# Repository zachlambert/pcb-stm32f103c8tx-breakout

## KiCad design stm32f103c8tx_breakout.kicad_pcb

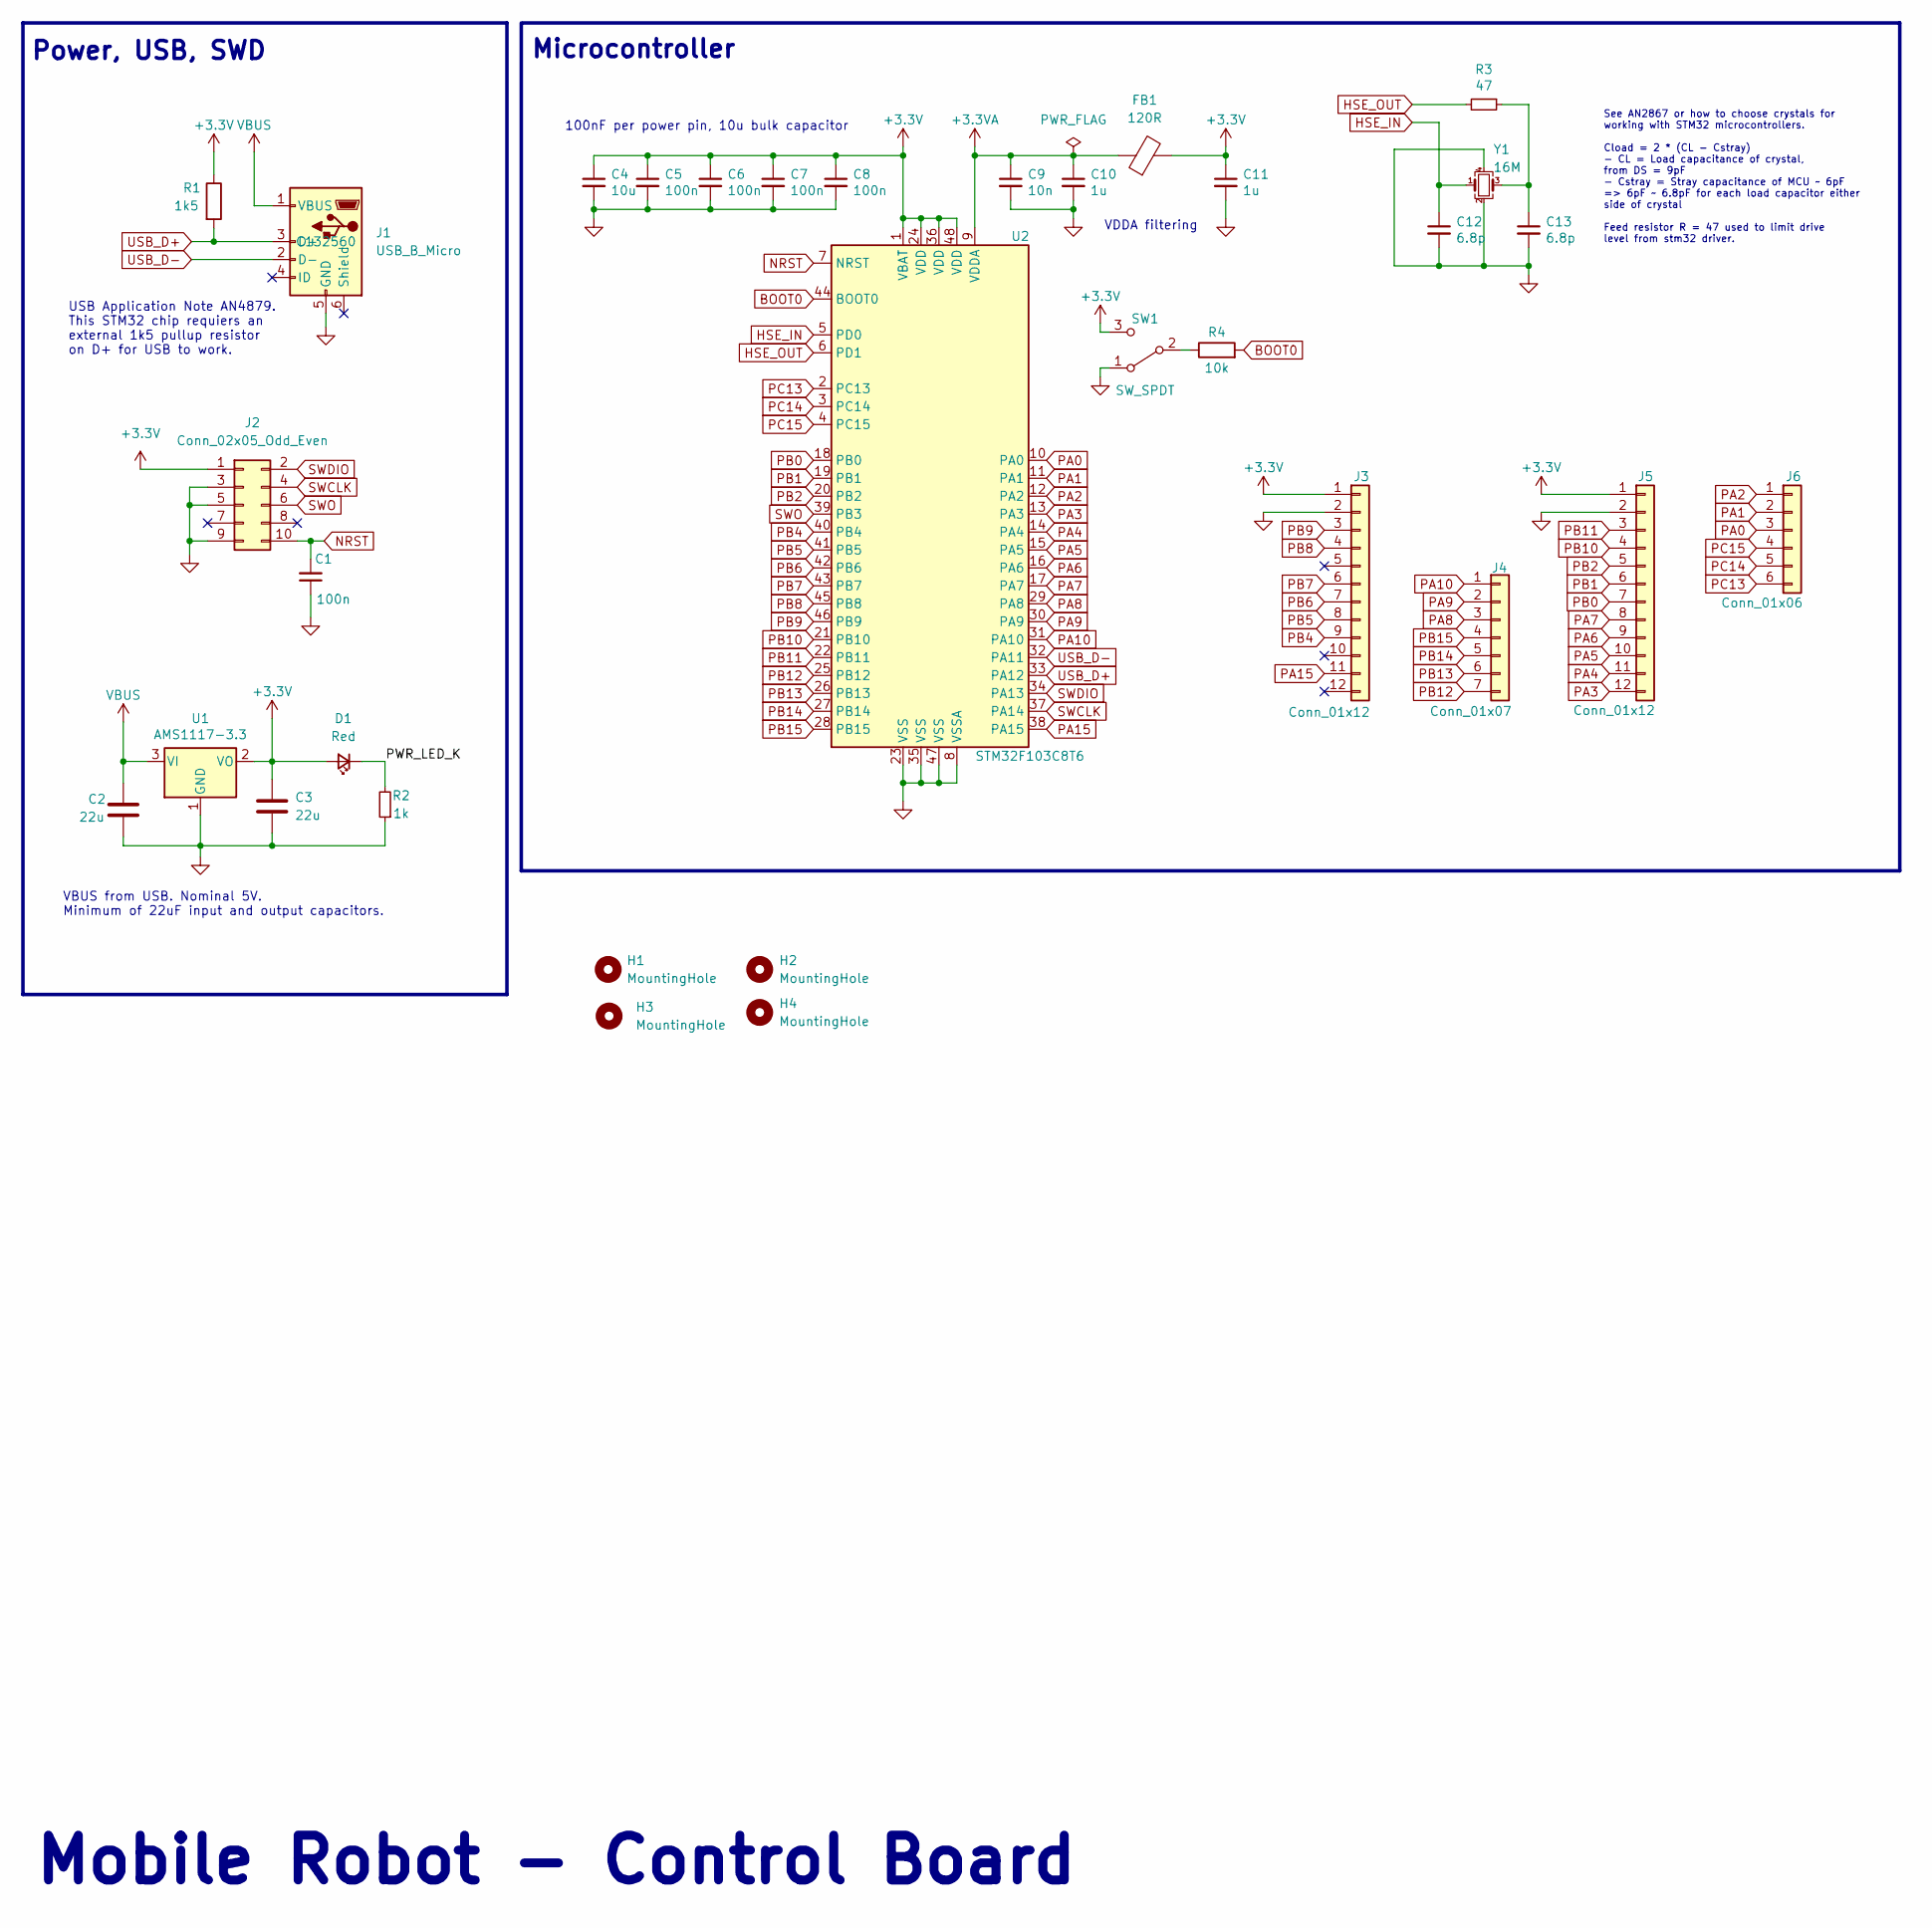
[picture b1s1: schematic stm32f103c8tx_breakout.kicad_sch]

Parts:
C1, C5, C6, C7, C8: 100n; C_0402_1005Metric
C2, C3: 22u; C_0805_2012Metric
C4: 10u; C_0603_1608Metric
C9: 10n; C_0402_1005Metric
C10, C11: 1u; C_0402_1005Metric
C12, C13: 6.8p; C_0402_1005Metric
D1: Red; D_0603_1608Metric
FB1: 120R; L_0603_1608Metric
H1, H2, H3, H4: MountingHole; MountingHole_3.2mm_M3
J1: USB_B_Micro; USB_Micro-B_Molex_47346-0001; LCSC C132560
J2: Conn_02x05_Odd_Even; PinHeader_2x05_P2.54mm_Vertical; LCSC C492422
J3, J5: Conn_01x12; PinSocket_1x12_P2.54mm_Vertical
J4: Conn_01x07; PinSocket_1x07_P2.54mm_Vertical
J6: Conn_01x06; PinSocket_1x06_P2.54mm_Vertical
R1: 1k5; R_0402_1005Metric
R2: 1k; R_0402_1005Metric
R3: 47; R_0402_1005Metric
R4: 10k; R_0402_1005Metric
SW1: SW_SPDT; SW_SPDT_PCM12
U1: AMS1117-3.3; SOT-223-3_TabPin2; LCSC C6186
U2: STM32F103C8T6; LQFP-48_7x7mm_P0.5mm; LCSC C8734
Y1: 16M; Crystal_SMD_3225-4Pin_3.2x2.5mm; LCSC C13738

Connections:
+3.3VA: C9.1, C10.1, FB1.1, U2.9 (VDDA)
+3V3: C3.1, C4.1, C5.1, C6.1, C7.1, C8.1, C11.1, D1.2 (A), FB1.2, J2.1, J3.1, J5.1, R1.1, SW1.3 (C), U1.2 (VO), U2.1 (VBAT), U2.24 (VDD), U2.36 (VDD), U2.48 (VDD)
/PWR_LED_K: D1.1 (K), R2.2
BOOT0: R4.2, U2.44 (BOOT0)
GND: C1.1, C2.2, C3.2, C4.2, C5.2, C6.2, C7.2, C8.2, C9.2, C10.2, C11.2, C12.2, C13.2, J1.5 (GND), J2.3, J2.5, J2.9, J3.2, J5.2, R2.1, SW1.1 (A), U1.1 (GND), U2.8 (VSSA), U2.23 (VSS), U2.35 (VSS), U2.47 (VSS), Y1.2, Y1.4
HSE_IN: C12.1, U2.5 (PD0), Y1.1
HSE_OUT: R3.2, U2.6 (PD1)
NRST: C1.2, J2.10, U2.7 (NRST)
unnamed: C13.1, R3.1, Y1.3
unnamed: R4.1, SW1.2 (B)
PA0: J6.3, U2.10 (PA0)
PA1: J6.2, U2.11 (PA1)
PA2: J6.1, U2.12 (PA2)
PA3: J5.12, U2.13 (PA3)
PA4: J5.11, U2.14 (PA4)
PA5: J5.10, U2.15 (PA5)
PA6: J5.9, U2.16 (PA6)
PA7: J5.8, U2.17 (PA7)
PA8: J4.3, U2.29 (PA8)
PA9: J4.2, U2.30 (PA9)
PA10: J4.1, U2.31 (PA10)
PA15: J3.11, U2.38 (PA15)
PB0: J5.7, U2.18 (PB0)
PB1: J5.6, U2.19 (PB1)
PB2: J5.5, U2.20 (PB2)
PB4: J3.9, U2.40 (PB4)
PB5: J3.8, U2.41 (PB5)
PB6: J3.7, U2.42 (PB6)
PB7: J3.6, U2.43 (PB7)
PB8: J3.4, U2.45 (PB8)
PB9: J3.3, U2.46 (PB9)
PB10: J5.4, U2.21 (PB10)
PB11: J5.3, U2.22 (PB11)
PB12: J4.7, U2.25 (PB12)
PB13: J4.6, U2.26 (PB13)
PB14: J4.5, U2.27 (PB14)
PB15: J4.4, U2.28 (PB15)
PC13: J6.6, U2.2 (PC13)
PC14: J6.5, U2.3 (PC14)
PC15: J6.4, U2.4 (PC15)
SWCLK: J2.4, U2.37 (PA14)
SWDIO: J2.2, U2.34 (PA13)
SWO: J2.6, U2.39 (PB3)
USB_D+: J1.3 (D+), R1.2, U2.33 (PA12)
USB_D-: J1.2 (D-), U2.32 (PA11)
VBUS: C2.1, J1.1 (VBUS), U1.3 (VI)

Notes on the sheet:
USB Application Note AN4879. This STM32 chip requiers an external 1k5 pullup resistor on D+ for USB to work.
VDDA filtering
Power, USB, SWD
See AN2867 or how to choose crystals for working with STM32 microcontrollers. Cload = 2 * (CL - Cstray) - CL = Load capacitance of crystal, from DS = 9pF - Cstray = Stray capacitance of MCU ~ 6pF => 6pF ~ 6.8pF for each load capacitor either side of crystal Feed resistor R = 47 used to limit drive 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
Mobile Robot - Control Board
100nF per power pin, 10u bulk capacitor
Microcontroller
VBUS from USB. Nominal 5V. Minimum of 22uF input and output capacitors.

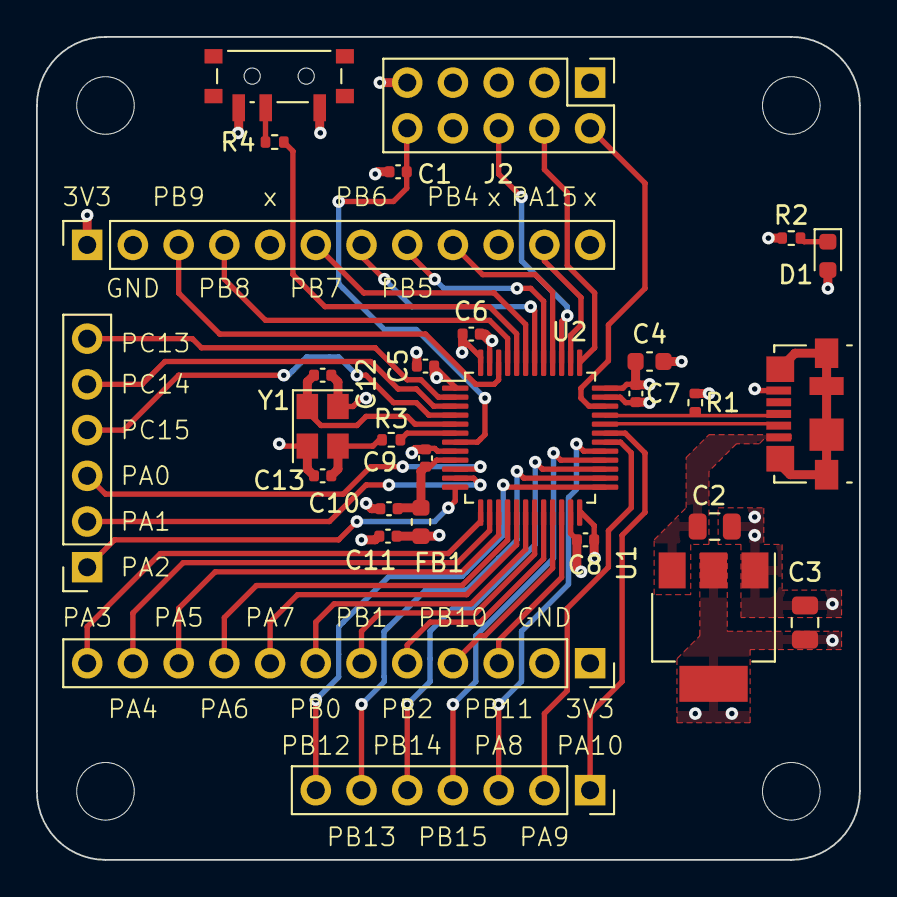
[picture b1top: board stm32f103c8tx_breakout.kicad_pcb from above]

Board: 4 copper layers, 45.7 x 45.7 mm, 33 parts (0 on the bottom side), 46 nets.

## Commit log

2022-08-05 Completed 2 layer board, going to try routing with 4 layers instead
2022-08-05 Changed routing to use 4 layers, with internal gnd and 3v3 planes
2024-06-17 Changes to fix for jlcpcb parts
